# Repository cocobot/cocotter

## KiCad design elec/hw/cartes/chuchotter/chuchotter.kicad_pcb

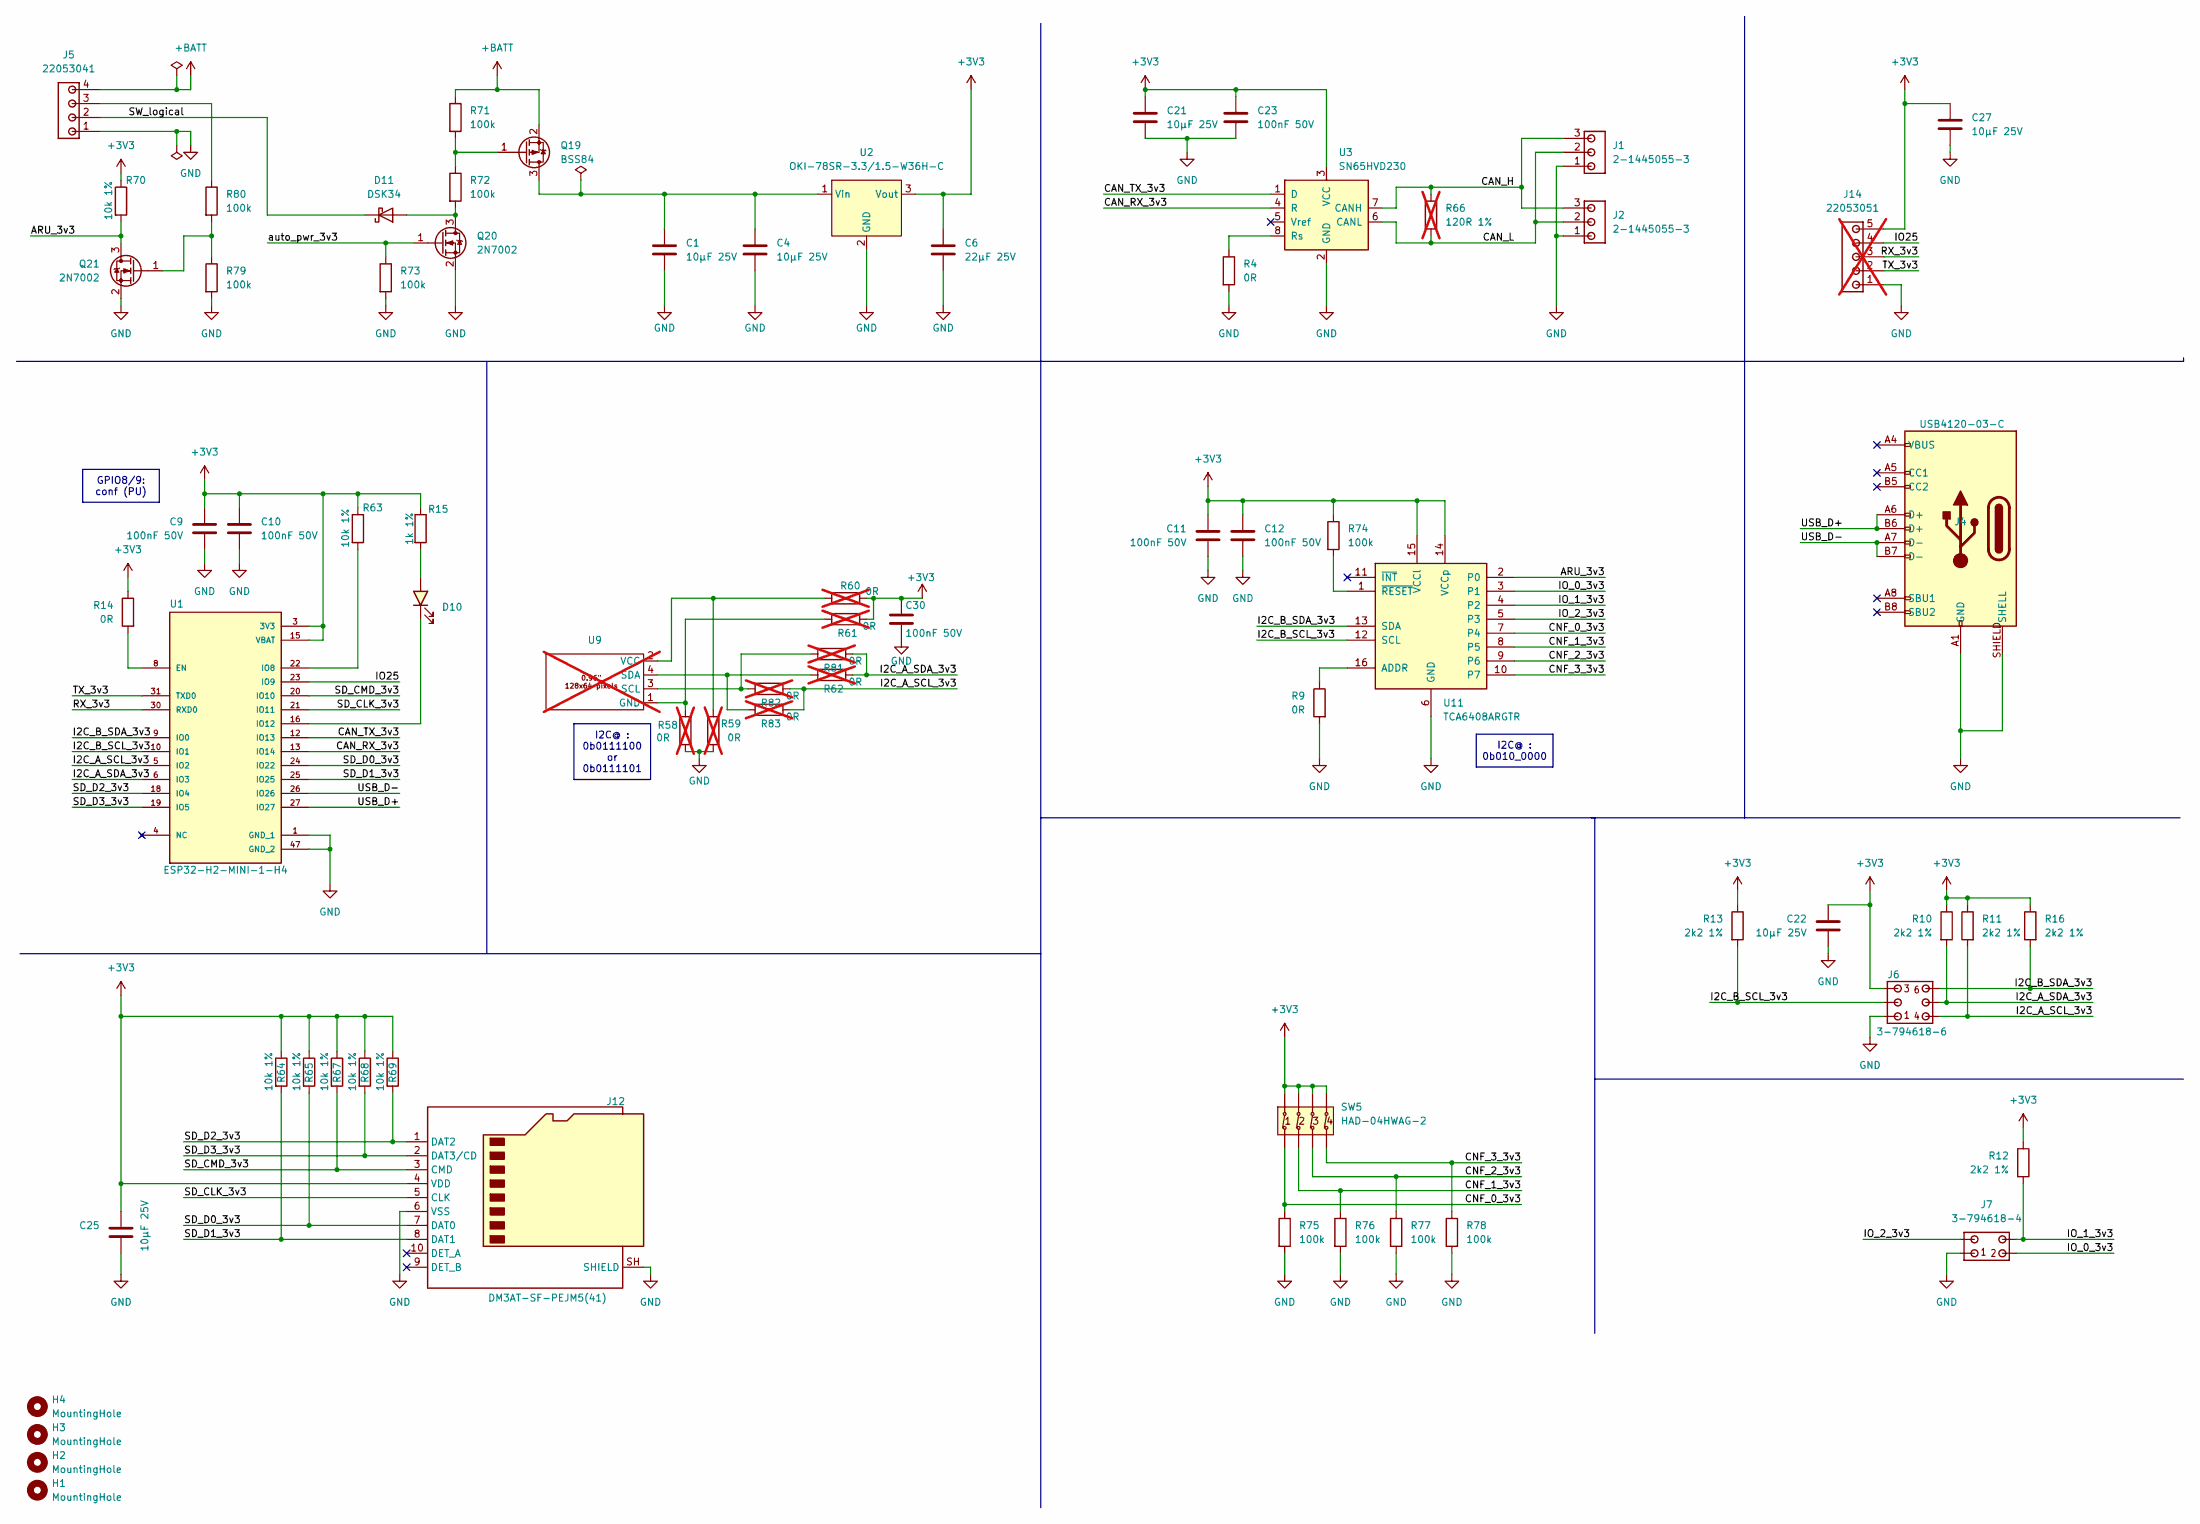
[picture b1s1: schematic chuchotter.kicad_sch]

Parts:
C1, C4, C21, C22, C25, C27: 10µF 25V; C_0805_2012Metric; JLCPCB Part # C15850
C6: 22µF 25V; C_1206_3216Metric; JLCPCB Part # C2918511
C9, C10, C11, C12, C23, C30: 100nF 50V; C_0603_1608Metric; JLCPCB Part # C14663
D10: green, 0603; LED_0603_1608Metric; DIGIKEY_REF 3147-B19Y1UYG-20C000313U1930CT-ND
D11: DSK34; D_SOD-123; JLCPCB Part # C727076
H1, H2, H3, H4: MountingHole; MountingHole_3.2mm_M3
J1, J2: 2-1445055-3; JLCPCB Part # C239447
J4: USB4120-03-C; JLCPCB Part # C7450621
J5: 22053041; JLCPCB Part # C5271241
J6: 3-794618-6; JLCPCB Part # C532085
J7: 3-794618-4
J12: DM3AT-SF-PEJM5(41); microSD_HC_Hirose_DM3AT-SF-PEJM5
J14: 22053051; PinHeader_1x05_P2.54mm_Vertical; JLCPCB Part # C586992; not fitted
Q19: BSS84; SOT-23-3
Q20, Q21: 2N7002; SOT-23-3; JLCPCB Part # C8545
R4, R9, R14: 0R; r0603_reflow; JLCPCB Part # C431718
R10, R11, R12, R13, R16: 2k2 1%; r0603_reflow; JLCPCB Part # C4190
R15: 1k 1%; r0603_reflow; JLCPCB Part # C2991540
R58, R59, R60, R61, R62, R81, R82, R83: 0R; r0603_reflow; JLCPCB Part # C431718; not fitted
R63, R64, R65, R67, R68, R69, R70: 10k 1%; r0603_reflow; JLCPCB Part # C25804
R66: 120R 1%; r1206_reflow; JLCPCB Part # C17909; not fitted
R71, R72, R73, R74, R75, R76, R77, R78, R79, R80: 100k; r0603_reflow; JLCPCB Part # C25803
SW5: HAD-04HWAG-2; JLCPCB Part # C437204
U1: ESP32-H2-MINI-1-H4; JLCPCB Part # C47967030
U2: OKI-78SR-3.3/1.5-W36H-C; OKI78SR-H
U3: SN65HVD230; SOIC-8_3.9x4.9mm_P1.27mm
U9: OLED_0.96inch; not fitted
U11: TCA6408ARGTR; VQFN-16-1EP_3x3mm_P0.5mm_EP1.1x1.1mm; JLCPCB part# C181499

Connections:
+3V3: C6.1, C9.1, C10.1, C11.1, C12.1, C21.1, C22.1, C23.1, C25.1, C27.1, C30.1, J6.3, J12.4 (VDD), J14.5, R10.1, R11.1, R12.1, R13.1, R14.1, R15.1, R16.1, R60.2, R61.2, R63.1, R64.1, R65.1, R67.1, R68.1, R69.1, R70.1, R74.1, SW5.5, SW5.6, SW5.7, SW5.8, U1.3 (3V3), U1.15 (VBAT), U2.3 (Vout), U3.3 (VCC), U11.14 (VCCp), U11.15 (VCCl)
+BATT: J5.4, Q19.2 (S), R71.1
/ARU_3v3: Q21.3 (D), R70.2, U11.2 (P0)
/CAN_H: J1.3, J2.3, R66.1, U3.7 (CANH)
/CAN_L: J1.2, J2.2, R66.2, U3.6 (CANL)
/CAN_RX_3v3: U1.13 (IO14), U3.4 (R)
/CAN_TX_3v3: U1.12 (IO13), U3.1 (D)
/CNF_0_3v3: R75.1, SW5.1, U11.7 (P4)
/CNF_1_3v3: R76.1, SW5.2, U11.8 (P5)
/CNF_2_3v3: R77.1, SW5.3, U11.9 (P6)
/CNF_3_3v3: R78.1, SW5.4, U11.10 (P7)
/I2C_A_SCL_3v3: J6.4, R11.2, R81.1, R82.1, R82.2, R83.2, U1.5 (IO2), U9.3 (SCL)
/I2C_A_SDA_3v3: J6.5, R10.2, R62.1, R62.2, R81.2, R83.1, U1.6 (IO3), U9.4 (SDA)
/I2C_B_SCL_3v3: J6.2, R13.2, U1.10 (IO1), U11.12 (SCL)
/I2C_B_SDA_3v3: J6.6, R16.2, U1.9 (IO0), U11.13 (SDA)
/IO25: J14.4, U1.23 (IO9)
/IO_0_3v3: J7.2, U11.3 (P1)
/IO_1_3v3: J7.4, R12.2, U11.4 (P2)
/IO_2_3v3: J7.3, U11.5 (P3)
/RX_3v3: J14.3, U1.30 (RXD0)
/SD_CLK_3v3: J12.5 (CLK), U1.21 (IO11)
/SD_CMD_3v3: J12.3 (CMD), R67.2, U1.20 (IO10)
/SD_D0_3v3: J12.7 (DAT0), R65.2, U1.24 (IO22)
/SD_D1_3v3: J12.8 (DAT1), R64.2, U1.25 (IO25)
/SD_D2_3v3: J12.1 (DAT2), R69.2, U1.18 (IO4)
/SD_D3_3v3: J12.2 (DAT3/CD), R68.2, U1.19 (IO5)
/SW_logical: D11.1 (K), J5.2
/TX_3v3: J14.2, U1.31 (TXD0)
/USB_D+: J4.A6 (D+), J4.B6 (D+), U1.27 (IO27)
/USB_D-: J4.A7 (D-), J4.B7 (D-), U1.26 (IO26)
/auto_pwr_3v3: Q20.1 (G), R73.1
GND: C1.2, C4.2, C6.2, C9.2, C10.2, C11.2, C12.2, C21.2, C22.2, C23.2, C25.2, C27.2, C30.2, J1.1, J2.1, J4.A1 (GND), J4.A12 (GND), J4.B1 (GND), J4.B12 (GND), J4.SHIELD (SHELL), J5.1, J6.1, J7.1, J12.6 (VSS), J12.SH (SHIELD), J14.1, Q20.2 (S), Q21.2 (S), R4.2, R9.2, R58.1, R59.2, R73.2, R75.2, R76.2, R77.2, R78.2, R79.2, U1.1 (GND_1), U1.2 (GND_1), U1.11 (GND_1), U1.14 (GND_1), U1.36 (GND_1), U1.37 (GND_1), U1.38 (GND_1), U1.39 (GND_1), U1.40 (GND_1), U1.41 (GND_1), U1.42 (GND_1), U1.43 (GND_1), U1.44 (GND_1), U1.45 (GND_1), U1.46 (GND_1), U1.47 (GND_2), U1.48 (GND_2), U1.49_1 (GND_2), U1.49_2 (GND_2), U1.49_3 (GND_2), U1.49_4 (GND_2), U1.49_5 (GND_2), U1.49_6 (GND_2), U1.49_7 (GND_2), U1.49_8 (GND_2), U1.49_9 (GND_2), U1.50 (GND_2), U1.51 (GND_2), U1.52 (GND_2), U1.53 (GND_2), U2.2 (GND), U3.2 (GND), U11.6 (GND)
unnamed: D10.A, R15.2
unnamed: D11.2 (A), Q20.3 (D), R72.2
unnamed: J4.A4 (VBUS), J4.A9 (VBUS), J4.B4 (VBUS), J4.B9 (VBUS)
unnamed: J5.3, R80.1
unnamed: C1.1, C4.1, Q19.3 (D), U2.1 (Vin)
unnamed: Q19.1 (G), R71.2, R72.1
unnamed: Q21.1 (G), R79.1, R80.2
unnamed: R14.2, U1.8 (EN)
unnamed: R63.2, U1.22 (IO8)
unnamed: D10.C, U1.16 (IO12)
unnamed: R4.1, U3.8 (Rs)
unnamed: R58.2, R61.1, U9.1 (GND)
unnamed: R59.1, R60.1, U9.2 (VCC)
unnamed: R9.1, U11.16 (ADDR)
unnamed: R74.2, U11.1 (~RESET)

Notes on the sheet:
I2C@ : 0b010_0000
GPIO8/9: conf (PU)
I2C@ : 0b0111100 or 0b0111101

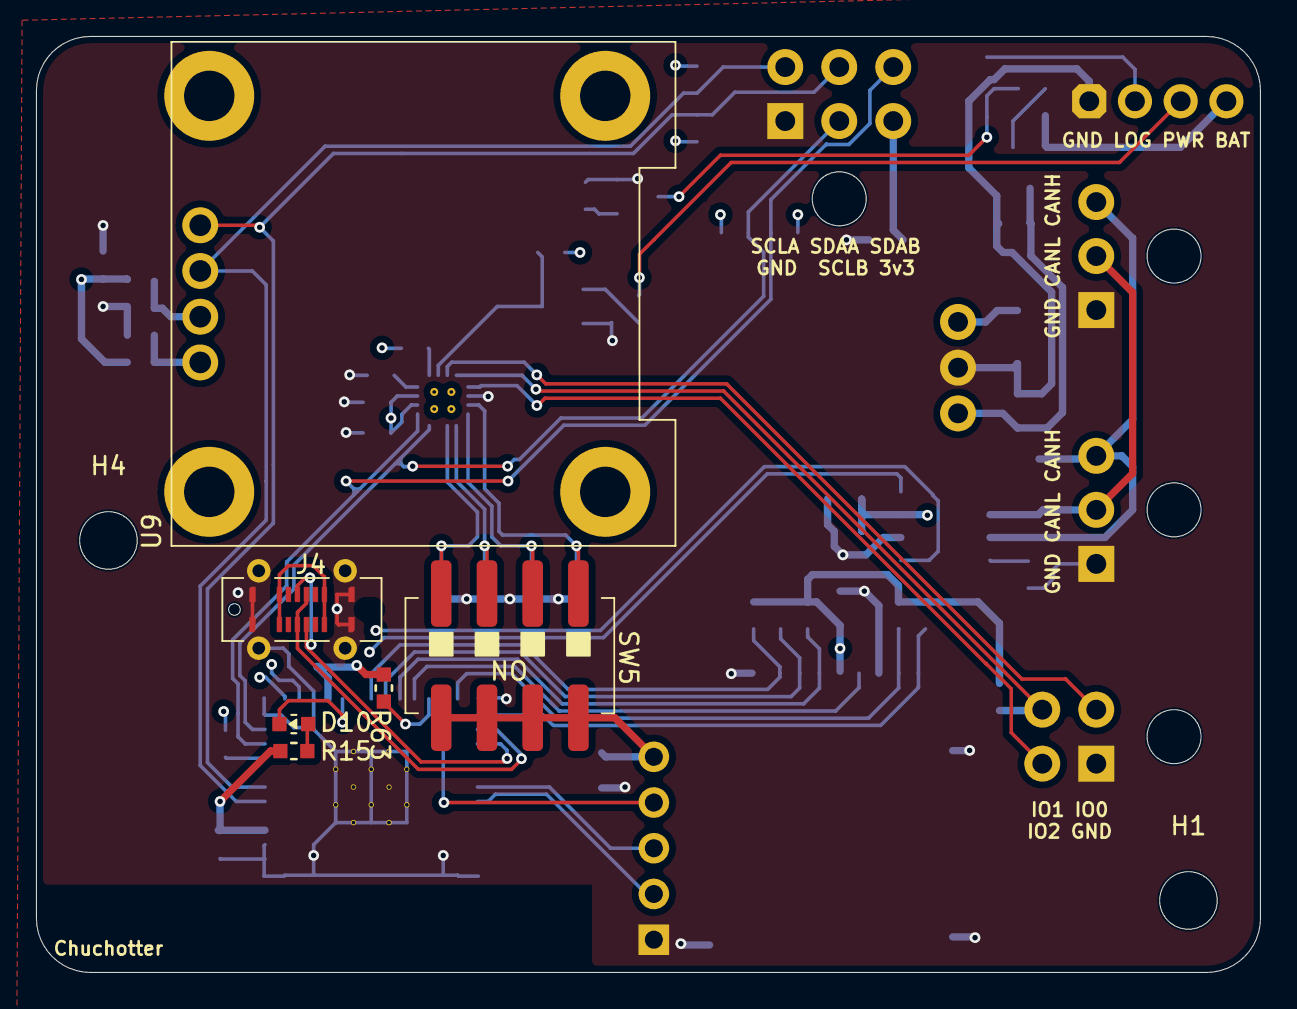
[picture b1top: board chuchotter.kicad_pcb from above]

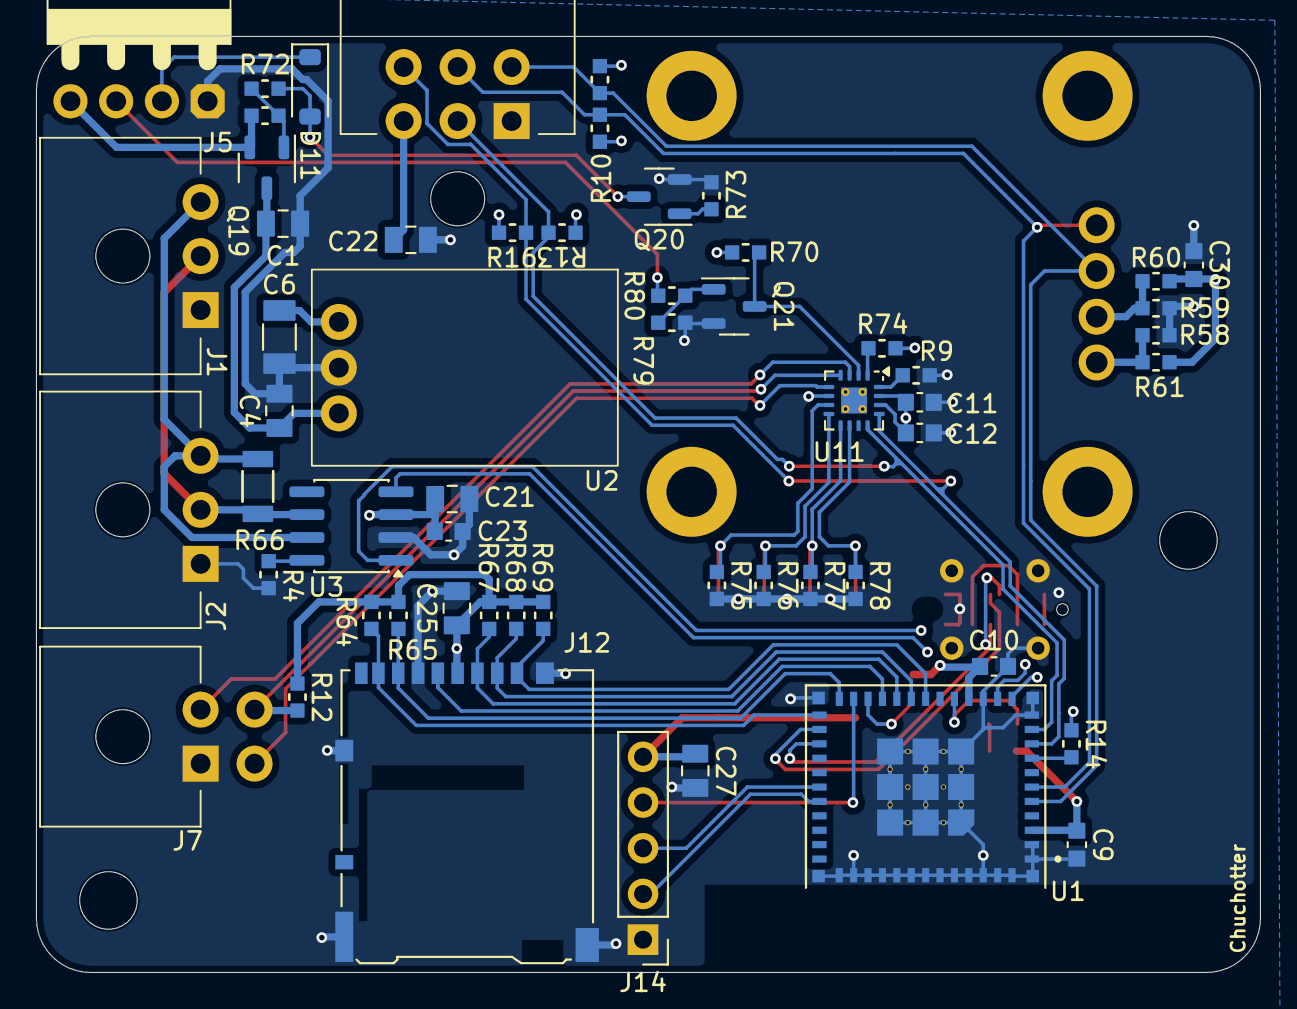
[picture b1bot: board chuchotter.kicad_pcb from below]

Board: 4 copper layers, 68.0 x 52.0 mm, 67 parts (57 on the bottom side), 47 nets.

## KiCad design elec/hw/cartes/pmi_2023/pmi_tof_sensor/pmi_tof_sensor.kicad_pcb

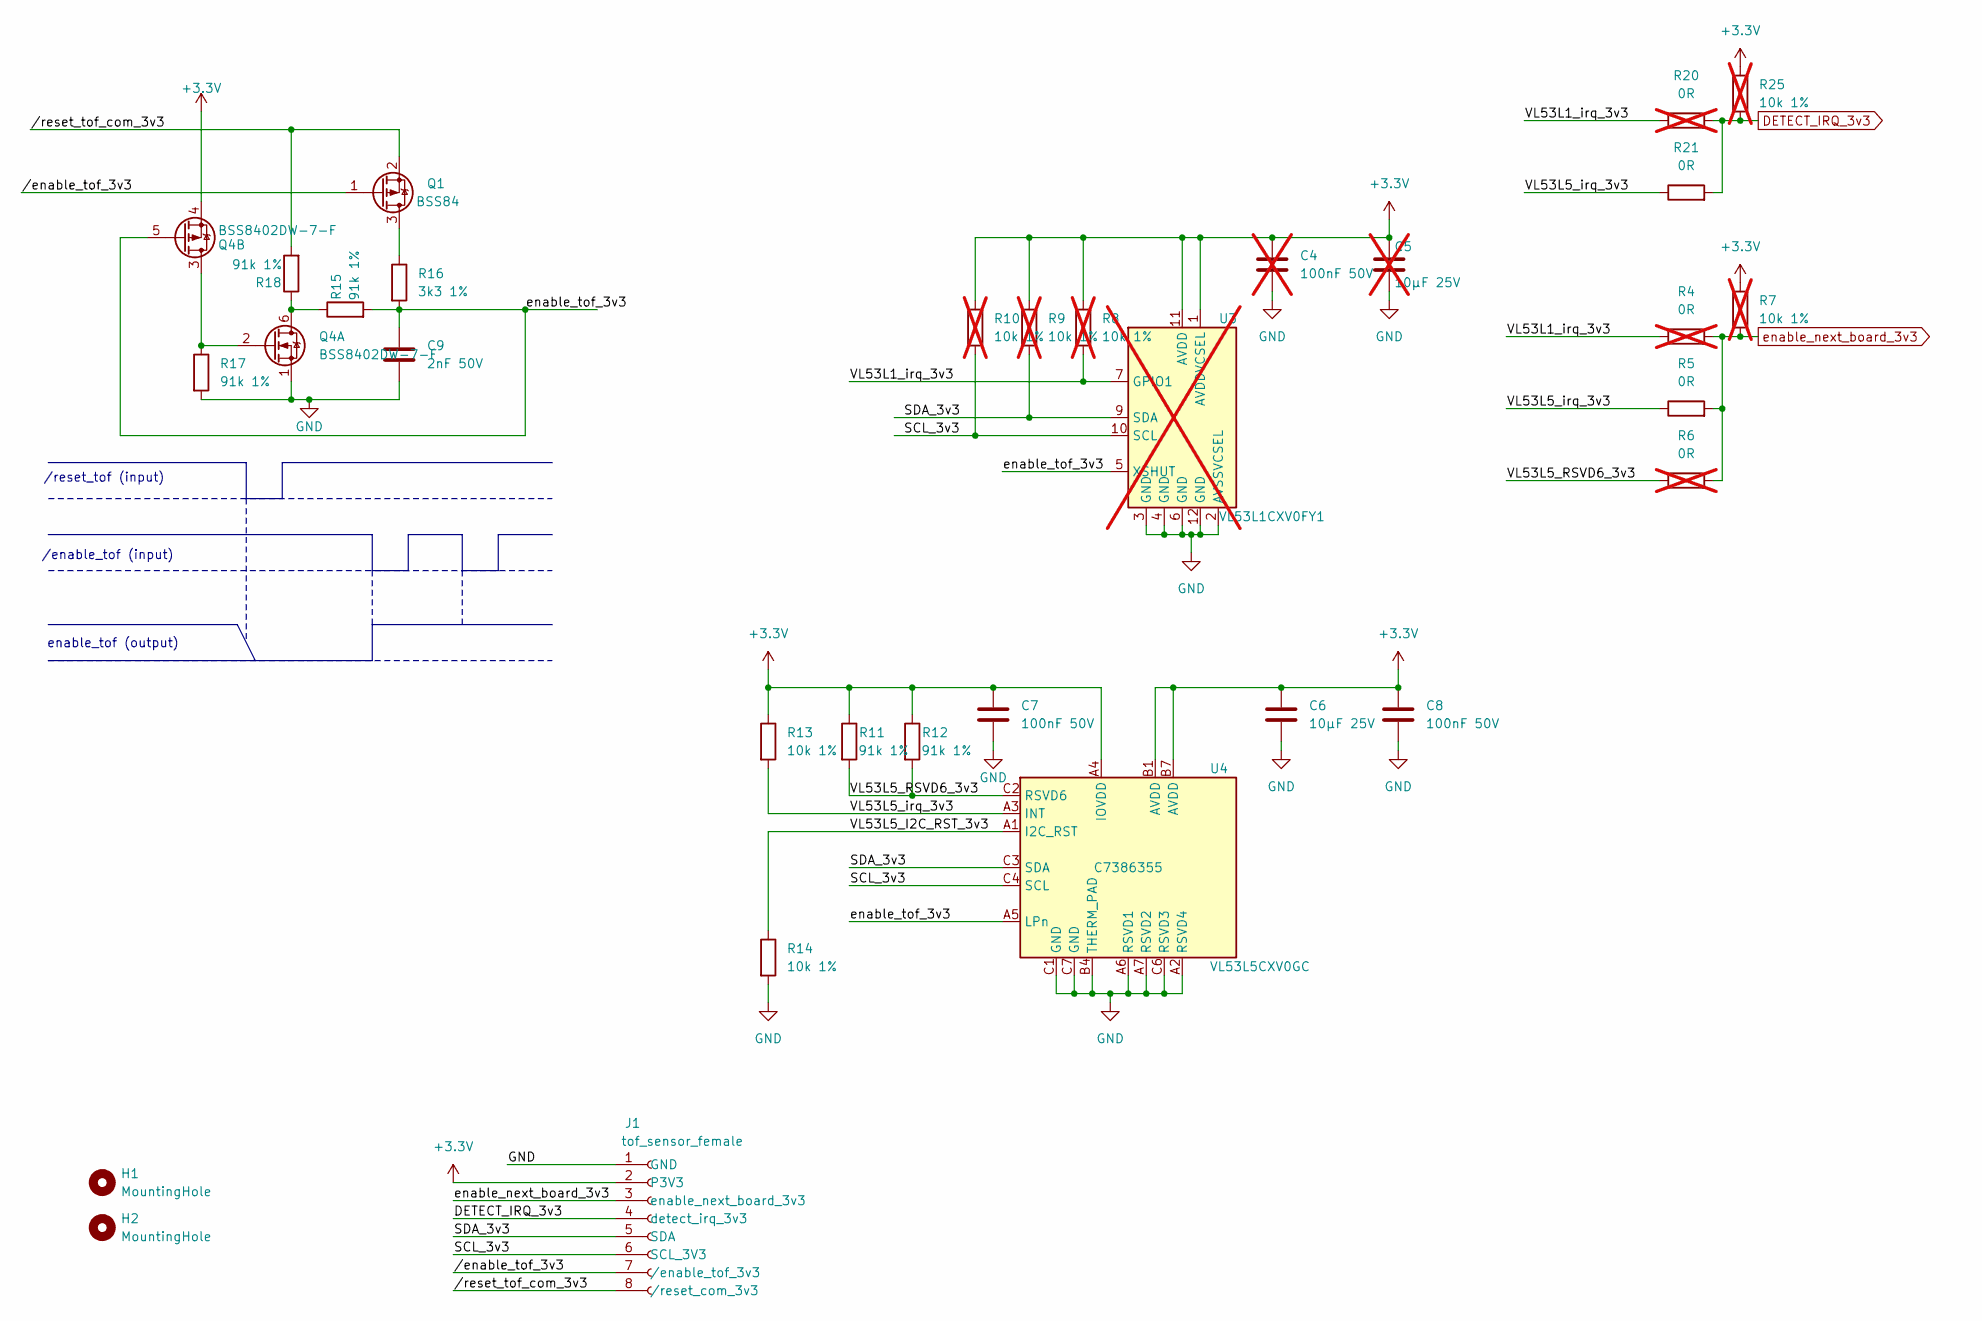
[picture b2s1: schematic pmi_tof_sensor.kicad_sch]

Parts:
C4: 100nF 50V; C_0603_1608Metric; JLCPCB C14663; not fitted
C5: 10µF 25V; C_0805_2012Metric; JLCPCB C15850; not fitted
C6: 10µF 25V; C_0805_2012Metric; JLCPCB C15850
C7, C8: 100nF 50V; C_0603_1608Metric; JLCPCB C14663
C9: 2nF 50V; C_0603_1608Metric; JLCPCB C1588
H1, H2: MountingHole; MountingHole_2.5mm-slot_1mm
J1: tof_sensor_female
Q1: BSS84; SOT-23-3
Q4: BSS8402DW-7-F; SOT-363_SC-70-6
R4, R6, R20: 0R; r0603_reflow; JLCPCB C431718; not fitted
R5, R21: 0R; r0603_reflow; JLCPCB C431718
R7, R8, R9, R10, R25: 10k 1%; r0603_reflow; mouser 603-RC0603FR-10100KL; not fitted
R11, R12, R15, R17, R18: 91k 1%; r0603_reflow; JLCPCB Part # C23265
R13, R14: 10k 1%; r0603_reflow; mouser 603-RC0603FR-10100KL
R16: 3k3 1%; r0603_reflow; JLCPCB C22978
U3: VL53L1CXV0FY1; ST_VL53L1x; JLCPCB C190004; not fitted
U4: VL53L5CXV0GC; VL53L5CX; JLCPCB C7386355

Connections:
+3.3V: C4.2, C5.1, C6.1, C7.1, C8.1, J1.2 (P3V3), Q4.4 (SP), R7.1, R8.1, R9.1, R10.1, R11.1, R12.1, R13.1, R25.1, U3.1 (AVDDVCSEL), U3.11 (AVDD), U4.A4 (IOVDD), U4.B1 (AVDD), U4.B7 (AVDD)
/SCL_3v3: J1.6 (SCL_3V3), R10.2, U3.10 (SCL), U4.C4 (SCL)
/SDA_3v3: J1.5 (SDA), R9.2, U3.9 (SDA), U4.C3 (SDA)
/VL53L1_irq_3v3: R4.1, R8.2, R20.1, U3.7 (GPIO1)
/VL53L5_I2C_RST_3v3: R14.1, U4.A1 (I2C_RST)
/VL53L5_RSVD6_3v3: R6.1, R11.2, R12.2, U4.C2 (RSVD6)
/VL53L5_irq_3v3: R5.1, R13.2, R21.1, U4.A3 (INT)
/enable_tof_3v3: C9.1, Q4.5 (GP), R15.2, R16.2, U3.5 (XSHUT), U4.A5 (LPn)
//enable_tof_3v3: J1.7 (/enable_tof_3v3), Q1.1 (G)
//reset_tof_com_3v3: J1.8 (/reset_com_3v3), Q1.2 (S), R18.2
DETECT_IRQ_3v3: J1.4 (detect_irq_3v3), R20.2, R21.2, R25.2
GND: C4.1, C5.2, C6.2, C7.2, C8.2, C9.2, J1.1 (GND), Q4.1 (SN), R14.2, R17.2, U3.2 (AVSSVCSEL), U3.3 (GND), U3.4 (GND), U3.6 (GND), U3.12 (GND), U4.A2 (RSVD4), U4.A6 (RSVD1), U4.A7 (RSVD2), U4.B4 (THERM_PAD), U4.C1 (GND), U4.C6 (RSVD3), U4.C7 (GND)
unnamed: Q1.3 (D), R16.1
unnamed: Q4.6 (DN), R15.1, R18.1
unnamed: Q4.2 (GN), Q4.3 (DP), R17.1
enable_next_board_3v3: J1.3 (enable_next_board_3v3), R4.2, R5.2, R6.2, R7.2

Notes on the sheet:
/enable_tof (input)
/reset_tof (input)
enable_tof (output)

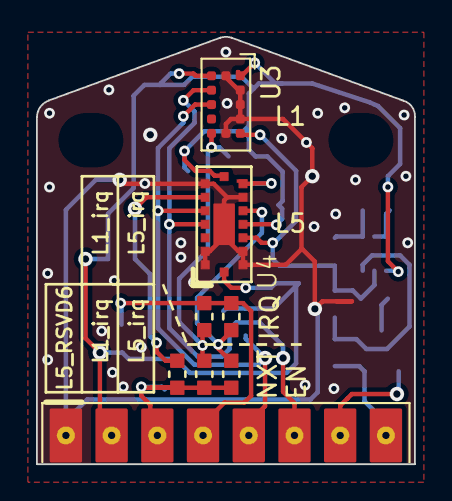
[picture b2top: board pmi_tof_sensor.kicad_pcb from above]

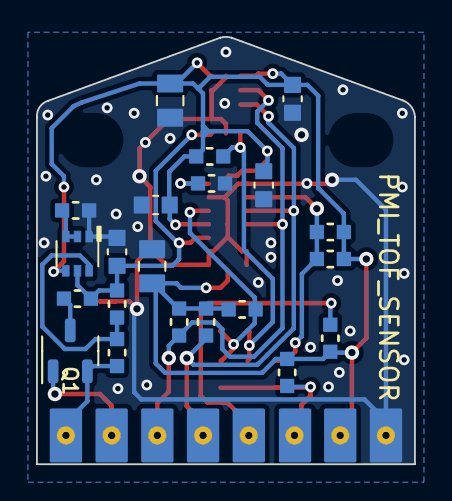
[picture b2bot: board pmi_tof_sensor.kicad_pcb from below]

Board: 2 copper layers, 21.0 x 23.7 mm, 31 parts (21 on the bottom side), 16 nets.

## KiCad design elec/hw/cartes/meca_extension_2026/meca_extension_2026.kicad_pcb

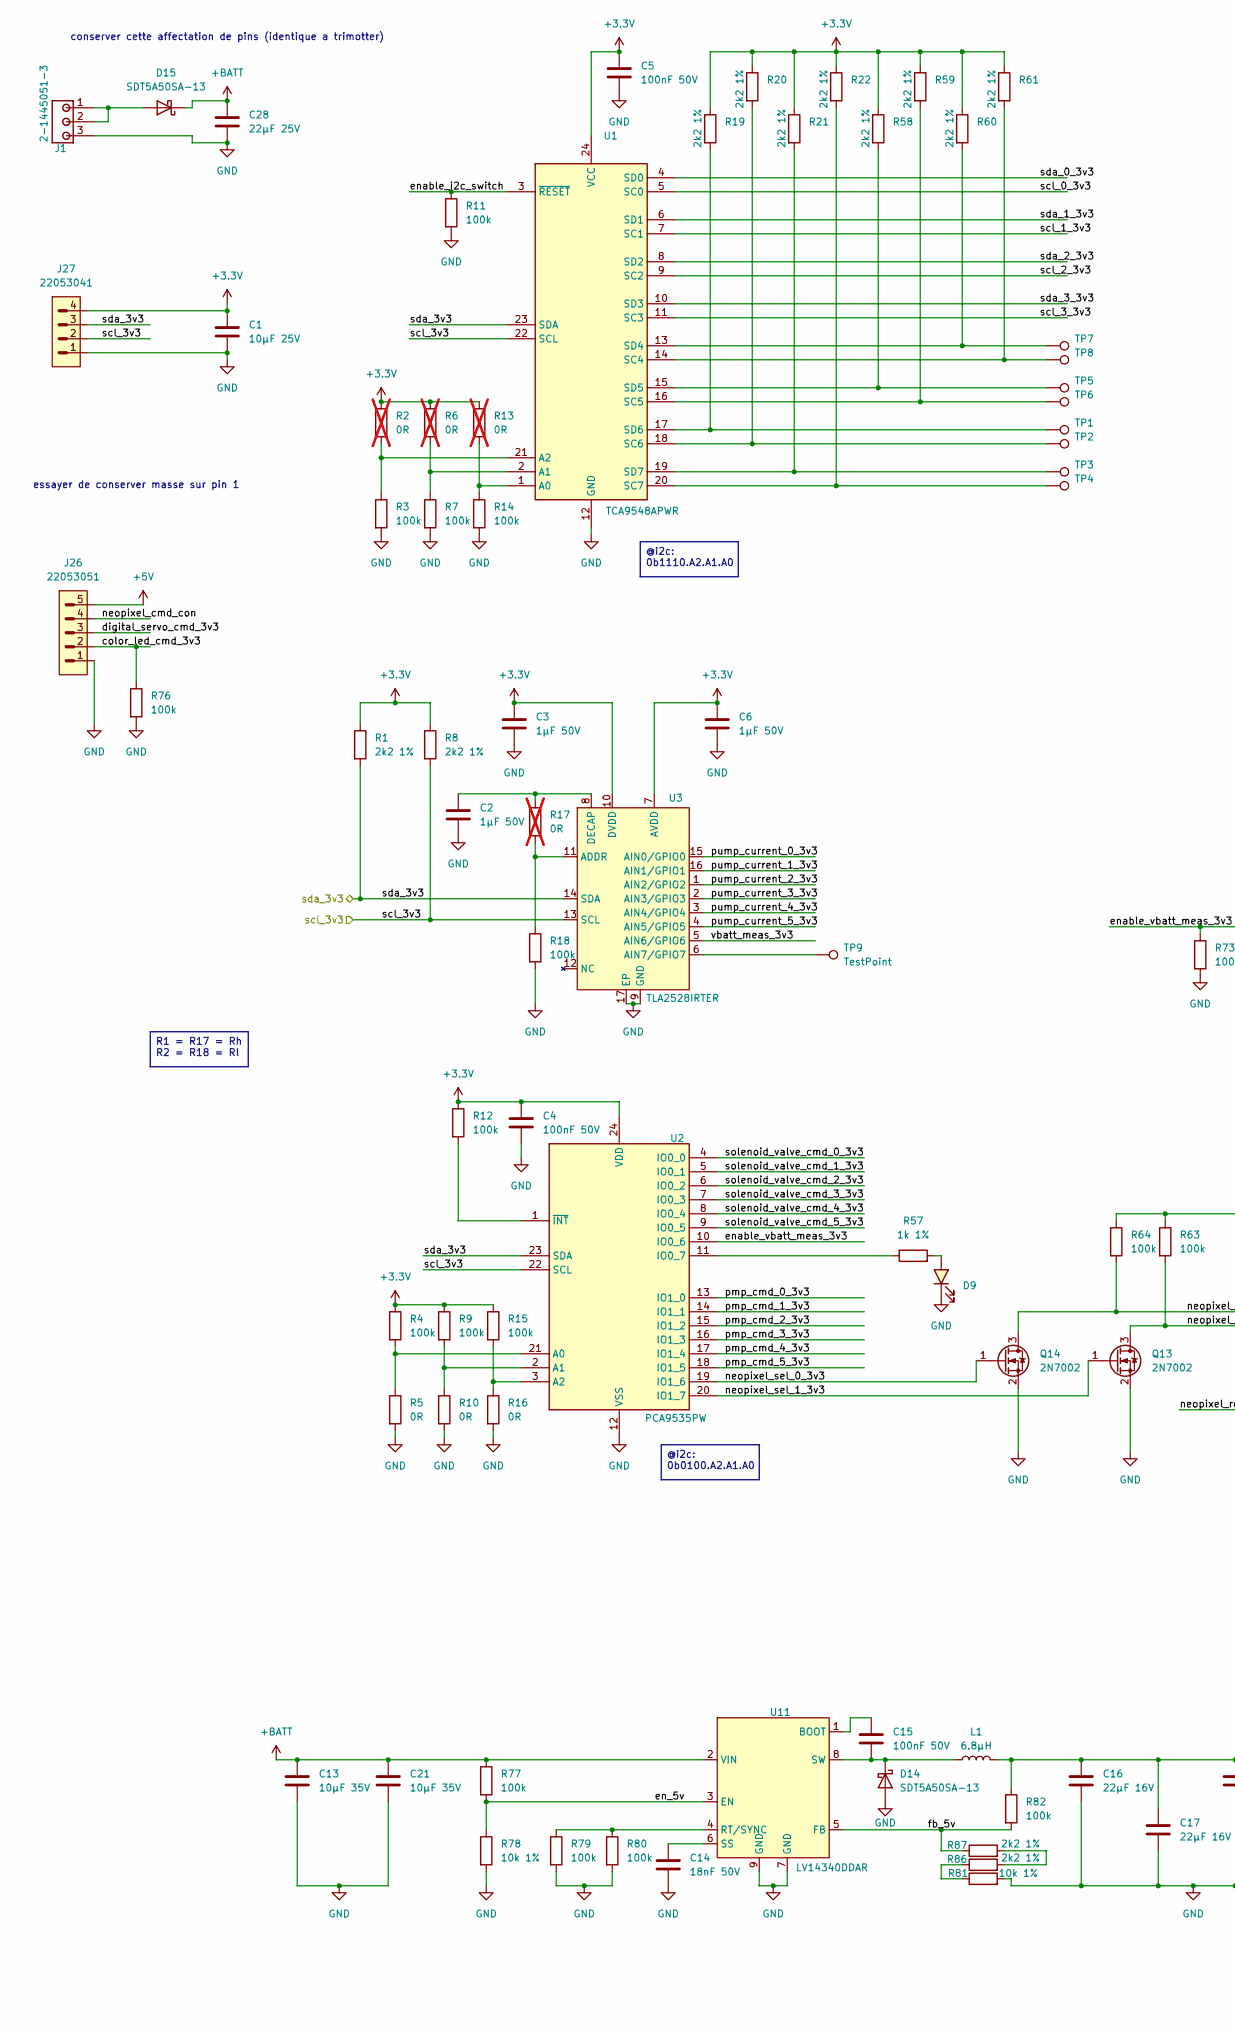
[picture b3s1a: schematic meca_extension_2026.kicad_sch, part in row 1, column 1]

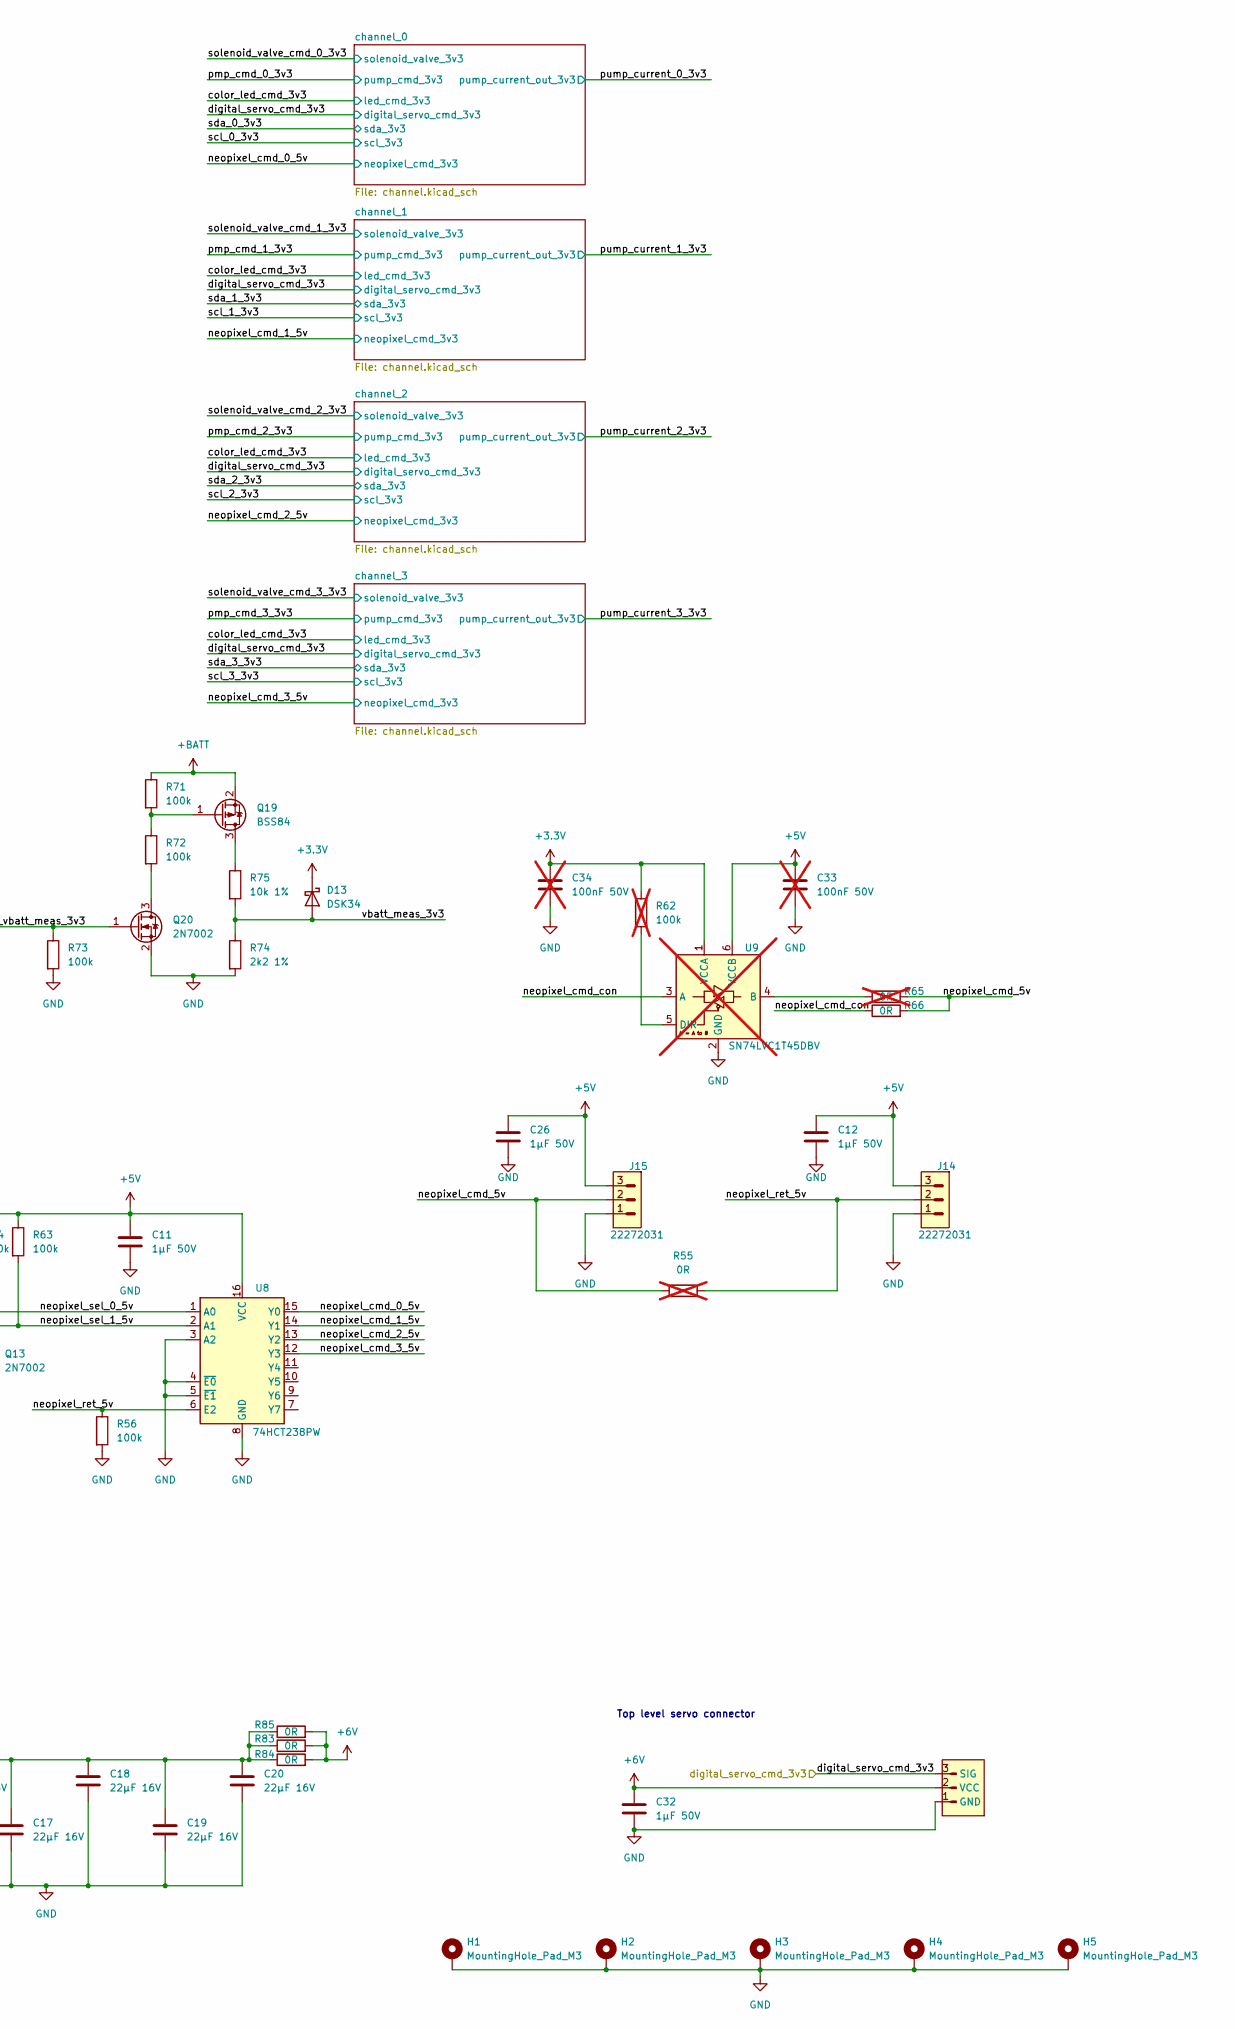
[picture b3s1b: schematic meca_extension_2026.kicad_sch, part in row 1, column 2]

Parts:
C1: 10µF 25V; C_0805_2012Metric; JLCPCB Part # C15850
C2, C3, C6, C11, C12, C26, C32: 1µF 50V; C_0805_2012Metric; JLCPCB Part # C28323
C4, C5, C15: 100nF 50V; C_0603_1608Metric; JLCPCB Part # C14663
C13, C21: 10µF 35V; C_1206_3216Metric; jlcpcb C454102
C14: 18nF 50V; C_0603_1608Metric; JLCPCB Part # C107079
C16, C17, C18, C19, C20: 22µF 16V; C_1206_3216Metric
C28: 22µF 25V; C_1206_3216Metric; JLCPCB Part # C2918511
C33, C34: 100nF 50V; C_0603_1608Metric; JLCPCB Part # C14663; not fitted
D9: yellow, 0603; LED_0603_1608Metric; DIGIKEY_REF 150060YS55040
D13: DSK34; D_SOD-123; JLCPCB Part # C727076
D14, D15: SDT5A50SA-13; D_SMA; JLCPCB Part # C6802582
H1, H2, H3, H4, H5: MountingHole_Pad_M3; MountingHole_3.2mm_M3_Pad_Via
J1: 2-1445051-3; JLCPCB Part # C17473329
J14, J15: 22272031; JLCPCB Part # C471416
J16: 5264-3P; JLC C49023819
J26: 22053051; 22272051; JLCPCB Part # C585785
J27: 22053041; 22272041; JLCPCB Part # C504991
L1: 6.8µH; BMRx00060630; JLCPCB Part # C2838323
Q13, Q14, Q20: 2N7002; SOT-23-3; JLCPCB Part # C8545
Q19: BSS84; SOT-23-3
R1, R8, R19, R20, R21, R22, R58, R59, R60, R61, R74, R86, R87: 2k2 1%; r0603_reflow; mouser 603-RC0603FR-10100KL
R2, R6, R13, R17, R55, R65: 0R; r0603_reflow; JLCPCB Part # C431718; not fitted
R3, R4, R7, R9, R11, R12, R14, R15, R18, R56, R63, R64, R71, R72, R73, R76, R77, R79, R80, R82: 100k; r0603_reflow; mouser 603-RC0603FR-10100KL
R5, R10, R16, R66, R83, R84, R85: 0R; r0603_reflow; JLCPCB Part # C431718
R57: 1k 1%; r0603_reflow; mouser 603-RC0603FR-10100KL
R62: 100k; r0603_reflow; mouser 603-RC0603FR-10100KL; not fitted
R75, R78, R81: 10k 1%; r0603_reflow; mouser 603-RC0603FR-10100KL
TP1, TP2, TP3, TP4, TP5, TP6, TP7, TP8, TP9: TestPoint; testpoint-THT-0.8mm
U1: TCA9548APWR; TSSOP-24_4.4x7.8mm_P0.65mm
U2: PCA9535PW; TSSOP-24_4.4x7.8mm_P0.65mm; JLCPCB Part # C42420616
U3: TLA2528IRTER; RTE0016C; JLCPCB Part # C2866175
U8: 74HCT238PW; TSSOP-16_4.4x5mm_P0.65mm; JLC# C547472
U9: SN74LVC1T45DBV; SOT-23-6; JLCPCB Part # C7843; not fitted
U11: LV14340DDAR; DDA0008B

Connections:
+3.3V: C1.1, C3.1, C4.1, C5.1, C6.1, C34.1, D13.1 (K), J27.4, R1.1, R2.1, R4.1, R6.1, R8.1, R9.1, R12.1, R13.1, R15.1, R19.1, R20.1, R21.1, R22.1, R58.1, R59.1, R60.1, R61.1, R62.1, U1.24 (VCC), U2.24 (VDD), U3.7 (AVDD), U3.10 (DVDD), U9.1 (VCCA); also elsewhere on the board
+5V: C11.1, C12.1, C26.1, C33.1, J14.3, J15.3, J26.5, R63.1, R64.1, U8.16 (VCC), U9.6 (VCCB); also elsewhere on the board
+6V: C32.1, J16.2 (VCC), R83.2, R84.2, R85.2; also elsewhere on the board
+BATT: C13.1, C21.1, C28.1, D15.1 (K), Q19.2 (S), R71.1, R77.1, U11.2 (VIN); also elsewhere on the board
/<NO NET>: Q13.1 (G), U2.20 (IO1_7)
/color_led_cmd_3v3: J26.2, R76.1; also elsewhere on the board
/digital_servo_cmd_3v3: J16.3 (SIG), J26.3; also elsewhere on the board
/en_5v: R77.2, R78.1, U11.3 (EN)
/enable_i2c_switch: R11.1, U1.3 (~RESET)
/enable_vbatt_meas_3v3: Q20.1 (G), R73.1, U2.10 (IO0_6)
/fb_5v: R82.2, R87.1, U11.5 (FB)
/neopixel_cmd_0_5v: U8.15 (Y0); also elsewhere on the board
/neopixel_cmd_1_5v: U8.14 (Y1); also elsewhere on the board
/neopixel_cmd_2_5v: U8.13 (Y2); also elsewhere on the board
/neopixel_cmd_3_5v: U8.12 (Y3); also elsewhere on the board
/neopixel_cmd_5v: J15.2, R55.1, R65.2, R66.2
/neopixel_cmd_con: J26.4, R66.1, U9.3 (A)
/neopixel_ret_5v: J14.2, R55.2, R56.1, U8.6 (E2)
/neopixel_sel_0_3v3: Q14.1 (G), U2.19 (IO1_6)
/neopixel_sel_0_5v: Q14.3 (D), R64.2, U8.1 (A0)
/neopixel_sel_1_5v: Q13.3 (D), R63.2, U8.2 (A1)
/pmp_cmd_0_3v3: U2.13 (IO1_0); also elsewhere on the board
/pmp_cmd_1_3v3: U2.14 (IO1_1); also elsewhere on the board
/pmp_cmd_2_3v3: U2.15 (IO1_2); also elsewhere on the board
/pmp_cmd_3_3v3: U2.16 (IO1_3); also elsewhere on the board
/pmp_cmd_4_3v3: U2.17 (IO1_4)
/pmp_cmd_5_3v3: U2.18 (IO1_5)
/pump_current_0_3v3: U3.15 (AIN0/GPIO0); also elsewhere on the board
/pump_current_1_3v3: U3.16 (AIN1/GPIO1); also elsewhere on the board
/pump_current_2_3v3: U3.1 (AIN2/GPIO2); also elsewhere on the board
/pump_current_3_3v3: U3.2 (AIN3/GPIO3); also elsewhere on the board
/pump_current_4_3v3: U3.3 (AIN4/GPIO4)
/pump_current_5_3v3: U3.4 (AIN5/GPIO5)
/scl_0_3v3: U1.5 (SC0); also elsewhere on the board
/scl_1_3v3: U1.7 (SC1); also elsewhere on the board
/scl_2_3v3: U1.9 (SC2); also elsewhere on the board
/scl_3_3v3: U1.11 (SC3); also elsewhere on the board
/scl_3v3: J27.2, R8.2, U1.22 (SCL), U2.22 (SCL), U3.13 (SCL)
/sda_0_3v3: U1.4 (SD0); also elsewhere on the board
/sda_1_3v3: U1.6 (SD1); also elsewhere on the board
/sda_2_3v3: U1.8 (SD2); also elsewhere on the board
/sda_3_3v3: U1.10 (SD3); also elsewhere on the board
/sda_3v3: J27.3, R1.2, U1.23 (SDA), U2.23 (SDA), U3.14 (SDA)
/solenoid_valve_cmd_0_3v3: U2.4 (IO0_0); also elsewhere on the board
/solenoid_valve_cmd_1_3v3: U2.5 (IO0_1); also elsewhere on the board
/solenoid_valve_cmd_2_3v3: U2.6 (IO0_2); also elsewhere on the board
/solenoid_valve_cmd_3_3v3: U2.7 (IO0_3); also elsewhere on the board
/solenoid_valve_cmd_4_3v3: U2.8 (IO0_4)
/solenoid_valve_cmd_5_3v3: U2.9 (IO0_5)
/vbatt_meas_3v3: D13.2 (A), R74.1, R75.2, U3.5 (AIN6/GPIO6)
GND: C1.2, C2.2, C3.2, C4.2, C5.2, C6.2, C11.2, C12.2, C13.2, C14.2, C16.2, C17.2, C18.2, C19.2, C20.2, C21.2, C26.2, C28.2, C32.2, C33.2, C34.2, D9.C, D14.2 (A), H1.1, H2.1, H3.1, H4.1, H5.1, J1.3, J14.1, J15.1, J16.1 (GND), J26.1, J27.1, Q13.2 (S), Q14.2 (S), Q20.2 (S), R3.2, R5.2, R7.2, R10.2, R11.2, R14.2, R16.2, R18.2, R56.2, R73.2, R74.2, R76.2, R78.2, R79.2, R80.2, R81.2, U1.12 (GND), U2.12 (VSS), U3.9 (GND), U3.17 (EP), U8.3 (A2), U8.4 (~E0), U8.5 (~E1), U8.8 (GND), U9.2 (GND), U11.7 (GND), U11.9 (GND); also elsewhere on the board
unnamed: C16.1, C17.1, C18.1, C19.1, C20.1, L1.2, R82.1, R83.1, R84.1, R85.1
unnamed: D9.A, R57.2
unnamed: C15.2, D14.1 (K), L1.1, U11.8 (SW)
unnamed: D15.2 (A), J1.1, J1.2
unnamed: Q19.3 (D), R75.1
unnamed: Q19.1 (G), R71.2, R72.1
unnamed: Q20.3 (D), R72.2
unnamed: R81.1, R86.1
unnamed: R86.2, R87.2
unnamed: R13.2, R14.1, U1.1 (A0)
unnamed: R6.2, R7.1, U1.2 (A1)
unnamed: R2.2, R3.1, U1.21 (A2)
unnamed: R61.2, TP8.1, U1.14 (SC4)
unnamed: R59.2, TP6.1, U1.16 (SC5)
unnamed: R20.2, TP2.1, U1.18 (SC6)
unnamed: R22.2, TP4.1, U1.20 (SC7)
unnamed: R60.2, TP7.1, U1.13 (SD4)
unnamed: R58.2, TP5.1, U1.15 (SD5)
unnamed: R19.2, TP1.1, U1.17 (SD6)
unnamed: R21.2, TP3.1, U1.19 (SD7)
unnamed: R4.2, R5.1, U2.21 (A0)
unnamed: R9.2, R10.1, U2.2 (A1)
unnamed: R15.2, R16.1, U2.3 (A2)
unnamed: R57.1, U2.11 (IO0_7)
unnamed: R12.2, U2.1 (~INT)
unnamed: R17.2, R18.1, U3.11 (ADDR)
unnamed: TP9.1, U3.6 (AIN7/GPIO7)
unnamed: C2.1, R17.1, U3.8 (DECAP)
unnamed: R65.1, U9.4 (B)
unnamed: R62.2, U9.5 (DIR)
unnamed: C15.1, U11.1 (BOOT)
unnamed: R79.1, R80.1, U11.4 (RT/SYNC)
unnamed: C14.1, U11.6 (SS)

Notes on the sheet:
conserver cette affectation de pins (identique a trimotter)
Top level servo connector
essayer de conserver masse sur pin 1
@i2c: 0b1110.A2.A1.A0
R1 = R17 = Rh R2 = R18 = Rl
@i2c: 0b0100.A2.A1.A0
